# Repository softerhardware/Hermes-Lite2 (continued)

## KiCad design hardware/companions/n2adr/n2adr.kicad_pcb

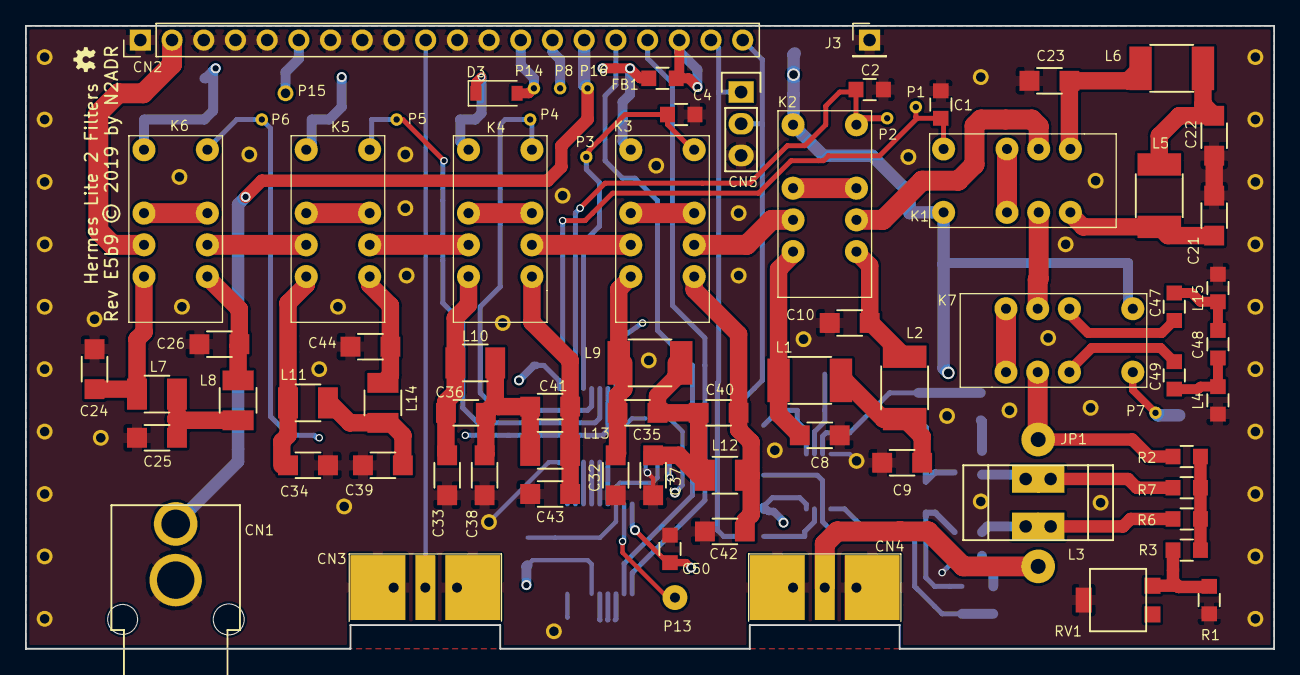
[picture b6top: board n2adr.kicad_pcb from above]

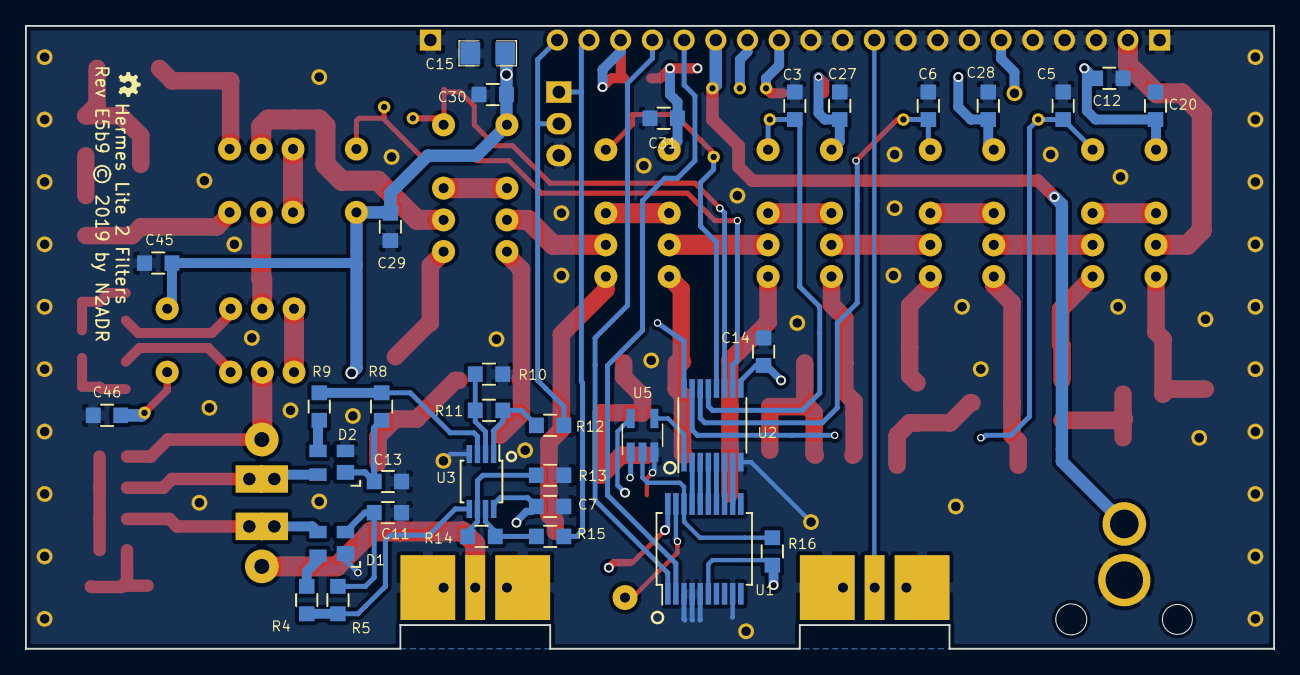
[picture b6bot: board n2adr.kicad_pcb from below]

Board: 4 copper layers, 100.0 x 49.9 mm, 112 parts (34 on the bottom side), 80 nets.

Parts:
C1, C2, C3, C4, C5, C6, C7, C11, C13, C14, C20, C27, C28, C29, C30, C31, C45, C46, C50: 100n; SMD_0805
C8, C10: 1000p; SMD_1206
C9, C21, C23: 1800p; SMD_1206
C12: 22uF; SMD_0805
C15: 100uF; SMD-1206
C22: 3300p; SMD_1206
C24, C26, C33: 150p; SMD_1206
C25, C39: 330p; SMD_1206
C32, C38, C40: 270p; SMD_1206
C34, C44: 180p; SMD_1206
C35: 100p; SMD_1206
C36: 39p; SMD_1206
C37: 560p; SMD_1206
C41, C42: 220p; SMD_1206
C43: 68p; SMD_1206
C47, C49: 1500p; SMD_0805
C48: 680p; SMD_0805
CN1: Audio-Jack-2; PhonoRcaRCJ-04x
CN2: Conn_01x20; Pin_Header_Straight_1x20_Pitch2.54mm
CN3, CN4: SMA; BNCEDGE
CN5: CONN_01X03; Pin_Header_Straight_1x03
D1, D2: BAS40-07; SOT-143
D3: 1N4148; D_SOD-123
FB1: FB; SMD_0805
J3: Conn_01x01; Pin_Header_Straight_1x01_Pitch2.54mm
JP1: 1T; WireConnection_1.20mmDrill
K1, K2, K3, K4, K5, K6, K7: EC2-3NU; RelayDPDT01
L1, L2: 1.8u; SMD_1812
L3: 10T; ToroidT37
L4, L15: 1.8u; SMD_0805
L5, L6: 3.9u; SMD_1812
L7, L8: 220n; SMD_1210
L9: 1000n; SMD_1812
L10: 560n; SMD_1210
L11, L14: 390n; SMD_1210
L12: 680n; SMD_1210
L13: 270n; SMD_1210
P1, P2, P3, P4, P5, P6, P7, P8, P14, P16: TST; WirePad_0.5mm
P13, P15: TST; SolderWirePad_single_0-8mmDrill
R1: 22 1%; SMD_0805
R2, R10, R13: 2K2 1%; SMD_0805
R3: 56 1%; SMD_0805
R4, R5, R8, R9: 4K7; SMD_0805
R6, R7: 18 1%; SMD_0805
R11, R14: 6K2 1%; SMD_0805
R12, R15: 330; SMD_0805
R16: DNI; SMD_0805
RV1: DNI; Trimpot_Bourns_3314G
U1: MCP23008; SSOP-20_5.3x7.2mm_Pitch0.65mm
U2: ULN2003LV; TSSOP-16_4.4x5mm_Pitch0.65mm
U3: AD8692; MSOP-8_3x3mm_Pitch0.65mm
U5: 74LVC1G00; SOT-23-5_HandSoldering

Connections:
+3V3: C7.2, C12.2, C14.2, C15.2, C20.2, C27.2, C28.2, C29.2, C30.2, C31.2, C45.2, C50.2, D3.1, FB1.1, K1.1, K2.1, K3.1, K4.1, K5.1, K6.1, K7.1, R16.1, U1.6, U1.20, U2.9, U3.8, U5.5
Band1: C1.2, K1.8, P1.1, U2.10
Band2: C2.2, K2.8, P2.1, U2.11
Band3: C4.2, K3.8, P3.1, U2.12
Band4: C3.2, K4.8, P4.1, U2.13
Band5: C6.2, K5.8, P5.1, U2.14
Band6: C5.2, K6.8, P6.1, U2.15
Band7: C46.2, K7.8, P7.1, U2.16
FilterOut: JP1.2, K7.6, R2.2
GND: C1.1, C2.1, C3.1, C4.1, C5.1, C6.1, C7.1, C8.1, C9.1, C10.1, C11.2, C12.1, C13.2, C14.1, C15.1, C20.1, C21.2, C22.2, C23.2, C24.1, C25.1, C26.1, C27.1, C28.1, C29.1, C30.1, C31.1, C32.1, C33.1, C34.1, C37.1, C38.1, C39.1, C42.1, C43.1, C44.1, C45.1, C46.1, C50.1, CN1.2, CN2.1, CN2.3, CN2.4, CN2.5, CN2.7, CN2.8, CN2.9, CN2.11, CN2.12, CN3.2, CN4.2, CN5.3, D1.1, D2.2, J3.1, L4.1, L15.1, R1.1, R10.1, R13.1, RV1.2, U1.3, U1.4, U1.5, U1.9, U2.8, U3.4, U5.3
INTTR: CN2.13, D3.2, P14.1, U5.1
unnamed: C8.2, K2.4, L1.1
unnamed: C9.2, L1.2, L2.1
unnamed: C10.2, K2.5, L2.2
unnamed: C11.1, D1.2, R5.2
unnamed: C13.1, D2.1, R8.2
unnamed: C21.1, K1.4, L5.1
unnamed: C22.1, L5.2, L6.1
unnamed: C23.1, K1.5, L6.2
unnamed: C24.2, K6.4, L7.1
unnamed: C25.2, L7.2, L8.1
unnamed: C26.2, K6.5, L8.2
unnamed: C32.2, C35.2, K3.4, L9.1
unnamed: C33.2, C36.2, K4.4, L10.1
unnamed: C34.2, K5.4, L11.1
unnamed: C35.1, C37.2, C40.2, L9.2, L12.1
unnamed: C36.1, C38.2, C41.2, L10.2, L13.1
unnamed: C39.2, L11.2, L14.1
unnamed: C40.1, C42.2, K3.5, L12.2
unnamed: C41.1, C43.2, K4.5, L13.2
unnamed: C44.2, K5.5, L14.2
unnamed: C47.1, C48.2, L15.2
unnamed: C47.2, K7.2
unnamed: C48.1, C49.2, L4.2
unnamed: C49.1, K7.7
unnamed: CN1.1, CN2.15, P16.1
unnamed: CN2.6, P15.1
unnamed: CN2.10, CN3.1
unnamed: CN2.14, P8.1
unnamed: CN2.16, U1.2
unnamed: CN2.17, U1.1
unnamed: CN2.18, FB1.2
unnamed: CN2.19, CN5.1, R15.2
unnamed: CN2.20, CN5.2, R12.2
unnamed: CN4.1, JP1.1
unnamed: D1.3, L3.1, R6.2
unnamed: D1.4, R4.2
unnamed: D2.3, R9.1
unnamed: D2.4, L3.2, R7.1
unnamed: K1.2, K1.7
unnamed: K1.3, K7.3
unnamed: K1.6, K2.6
unnamed: K2.2, K2.7
unnamed: K2.3, K3.6
unnamed: K3.2, K3.7
unnamed: K3.3, K4.6
unnamed: K4.2, K4.7
unnamed: K4.3, K5.6
unnamed: K5.2, K5.7
unnamed: K5.3, K6.6
unnamed: K6.2, K6.7
unnamed: K7.4, K7.5
unnamed: P13.1, U1.19
unnamed: R1.2, R3.1, RV1.1
unnamed: R2.1, R3.2, R6.1, R7.2
unnamed: R4.1, R5.1, U3.5
unnamed: R8.1, R9.2, U3.3
unnamed: R10.2, R11.1, U3.2
unnamed: R11.2, R12.1, U3.1
unnamed: R13.2, R14.1, U3.6
unnamed: R14.2, R15.1, U3.7
unnamed: R16.2, U1.18, U5.2
unnamed: U1.12, U2.7
unnamed: U1.13, U2.6
unnamed: U1.14, U2.5
unnamed: U1.15, U2.4
unnamed: U1.16, U2.3
unnamed: U1.17, U2.2
unnamed: U2.1, U5.4
RFInput: CN2.2, K6.3

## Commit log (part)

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2019-11-19 Rev 2 of rear end plate
2019-11-19 Swap horizontal and veritical lettering
2019-11-21 Rear end plate 40mm 2.0
2019-11-23 Updates to endplate
2019-11-24 55mm rev2 endplate
2019-11-25 Added pullups, diodes to some channels
2019-11-27 Added db9 adapter and smallio
2019-11-27 Updated hermeslite.lib
2019-11-30 Added io_jumper and psfeedback boards
2019-12-02 Final IO end plates
2019-12-02 Added BOM and generated gerber files
2019-12-02 Deleted old releases
2019-12-21 radioberry firmware and gateware added. 4rx (48k) and 1 tx (initial version)
2019-12-21 git ignore added
2019-12-21 build results removed
2019-12-22 making radioberry variants
2019-12-23 Assembly updates
2019-12-23 Assembly edits
2019-12-24 Added more assembly notes
2019-12-24 Fixed file name
2019-12-30 Added IO diagrams
2019-12-30 Added wiring diagram, increased PCB size
2019-12-30 Moved picture
2020-01-01 Added sym-lib-table and updated .sch to use only n2adr.lib
2020-01-08 improvement
2020-01-13 Added fan control, psync as generate, board id in discovery, fifo fixes
2020-01-18 Timing path fix in vna_scanner
2020-01-20 Stable release of 20191110_68p4, testing release of 20190119_69p0
2020-01-25 radioberry: use of iq fifo improved
2020-01-25 radioberry: tx and some improvements
2020-02-03 Fix for receivers number of 2,3,5 and 6
2020-02-03 Fix link
2020-02-03 radioberry build for new radio.v
2020-02-09 tx improvement
2020-02-11 First CWX support
2020-02-13 Release 69p2
2020-02-13 Added cw_openhpsdr
2020-02-14 Added cw_basic and led_flash
2020-02-22 Work on restructured FSM for TX
2020-02-23 20200222_69p3 release
2020-02-23 Updated 69p3 release notes
2020-03-01 cwx supported by radioberry
2020-03-02 Multi RX 3 working again, updates for autotuner, 69.4 testing
2020-03-02 ATU details
2020-03-02 Testing release 69.4
2020-03-06 radioberry 69p4
2020-03-09 Updated end plate README
2020-03-22 Add LPF for fan on latest end plates
2020-03-22 Support for factory and field gateware images in EEPROM
2020-03-23 Minor updates to schematic text
2020-03-23 Parameterized fast LNA, only set during RX
2020-03-28 Working LNA adjust during TX
2020-03-30 Release 20200329
2020-03-30 Release 20200329 bitfiles
2020-03-30 Change in size to SMA cutout
2020-03-31 Added missing remote_update.v
2020-04-21 Relax factory test
2020-04-21 Allow scaling of coefL4
2020-04-21 fan changes
2020-04-21 cwx fix to not accumulate data in TX buffer
2020-04-25 20200425_71p1 release
2020-04-26 Update hl2setup program for next production run
2020-04-28 gateware 71.1; LNA gain fast + CWX update
2020-05-03 Alex rx antenna
2020-05-04 revert fast LNA and increased tx pwr
2020-05-05 updated timing
2020-05-06 Switched to IAMP TX gain based on Hermes-Lite 1
2020-05-07 Radioberry TX; (version 71.3)
2020-05-16 Tighten timing on PGA5
2020-05-16 Simulation cleanup, add parameter to debug RX
2020-05-17 20200516_71p2 release
2020-05-23 Relaxed no filter 160M test
2020-05-29 Output register for UART
2020-05-29 Fix for no CW in SDR Console
2020-05-29 Fix for github issue 145
2020-05-30 71p3 and support to reset Versa5
2020-05-30 Release 71p3
2020-06-05 Added link to HR50 notes
2020-06-08 71p4 + ptt/key info to firmware/SDR program
2020-06-29 Moved 71p3 to stable, built all variants, clean-up of variants
2020-06-29 Ready for 72 series with hl2link
2020-06-30 2020069 72p0 relesae
2020-06-30 added and modified files for AK4951 Companion Board Version 3
2020-07-01 Updates to ak4951 variant to use generate, rerelease of hl2b5up_6rx
2020-07-01 Added hl2b3to4_cicrx and hl2b5up_15ce
2020-07-05 Added ak4951v3
2020-07-07 keyer CW
2020-07-11 i2c with clock sync working
2020-07-13 Experimental Release
    Please enter the commit message for your changes. Lines starting
2020-07-24 First working discovery on second ethernet port, updates to hl2link
2020-07-25 Reformat and align RTL
2020-07-25 Switch CDC in udp_destination to one way handshake
2020-07-27 Added extra discover fields, fixed ARP CDC, extra byte in UDP
2020-07-28 20200727_72p2 testing release
2020-08-04 Working response with port 1025
2020-08-04 Added hermeslite.py
2020-08-04 Release 20200803_72p3
2020-08-23 Updated hermeslite.py, added stable/latest link
2020-08-23 Fixed github gateware update
2020-08-23 Updated hermeslite.py README.md
2020-08-23 Fixed typos
2020-08-23 Proper typo fixes
2020-08-24 Updated hermeslite.py, added Jupyter notebook
2020-09-14 Synchronized command passing over link working
2020-09-19 New command mapping for sync and clock use
2020-09-20 Work on receive RX data in master
2020-09-28 Slave receive properly passed to master
2020-10-19 72p4 release
2020-10-19 move to archive
2020-10-19 Added 72p4 bitfiles
2020-11-01 Added receiver_4000
2020-11-03 Updated Band Volts to co-exist with Fan PWM. Selection via Dither bit.
2020-11-03 Adjusted for 3.3V power supply
2020-11-03 Added band voltage PWM output.
2020-11-08 Added keyup to CWX, increased watchdog timeout
2020-11-08 Restructured to avoid timing path
2020-11-08 Added write_ad9866
2020-11-08 20201107_72p5 testing release
2020-11-12 gateware 72.1
2020-11-12 gateware 72
2020-11-14 radioberry; gateware 72.2; local CW pihpsdr; using RB connector(CN301) to connect paddle
2020-11-16 72.3 radioberry; sync channel changes
2020-11-16 4k radioberry
2020-11-22 Add option to enable debug instrumentation
2020-11-22 Support for new debug instrumentation
2020-11-22 20201121_72p6 release
2020-11-22 Corrected syntax
2020-11-26 Added heatshim
2020-11-28 Initial attempt to improve the DHCP handling.
2020-11-28 Make sure that we revert to doing a DHCP discover after the network cable is unplugged and reconnected. Also, ask, in the DHCP DISCOVER for the IP address that we want.
    Also, don't respond to pings that are unicast to us when the IP address
    doesn't match. This fixes a problem where the DHCP server thinsks that
    our requested address is already in use by another system!
2020-11-28 192kHz cic only 10 receivers
2020-11-28 Release 72p7
2020-12-01 Use the configured IP to set the client address. Also include the ip_id so that we can count IP packets being sent to see where they are lost.
2020-12-01 Rename a poorly named signal
2020-12-03 Removed ip_id to fix timing
2020-12-06 radioberry 72.4
2020-12-09 Removed numpy from debug, small changes to hermeslite.py
2020-12-09 Updates to hl2link for sync receivers
2020-12-09 hl2b3to4 10rx working
2020-12-09 Added VERSA_BYPASS parameter for new variant
2020-12-13 TX buffer latency to 20ms, PTT Hangtime to 12ms
2020-12-13 HL2 Link refinements for synced receivers
2020-12-13 Prepare for 72.8 release
2020-12-13 20201212_72p8 release
2020-12-17 FAN/ATU clarifications
    Clearing up some items that tripped me up.
2020-12-19 Moved 20201212_72p8 to stable, fixes in hermeslite.py
2020-12-19 radioberry 72.5 version
2020-12-24 radioberry 4k
2020-12-31 Adjust value to get the port number correctly.
2020-12-31 Fix the use of tabs
2020-12-31 Improve the comment
2021-01-02 Add ft8 work
2021-01-03 added my endcaps with higher airflow
2021-01-05 ft8 work
2021-01-09 Added Python fortran wrapper
2021-02-16 radioberry gateware 73.0; support of PA board
2021-03-30 Added bypassversa
2021-04-29 Changed initialisation of tx_gain to reflect initialised value in ad9866.
2021-05-10 link updates, includes crc
2021-05-10 Added support to stay in TX mode until software says to go to RX
2021-05-10 73p0 testing release
2021-05-16 New testing with debug enabled
2021-05-16 Testing release 20210516_73p1
2021-06-24 gateware-radioberry-juice
2021-07-08 hermeslite.py: discover HL2s on all interfaces
2021-07-10 Added 10MHz config to Clk1 and Clk2
    In 1 new function, Clk1 is configured for external 10Mhz clock source and then Clk2 is configure to output 10Mhz, useful for chaining the 10Mhz on to a transverter or test equipment. This appears to 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
2021-07-10 Configure both Clk1 and Clk2 to 10Mhz in one function
2021-07-22 Merged 10MHz setup from K7MDL
2021-07-31 73p2 Testing Release
2021-08-05 20210730_73p2 release with all variants
2021-08-09 Moved 20210730_73p2 to stable
2021-08-19 Update README.md
    Removed 'testing' from README now that is is moved to 'stable'.
2021-08-28 juice tx without preamp
2021-09-11 radioberry 73.2 8bits rx + tx spi
2021-09-12 replaced sidetone module to reduce FPGA resources and revive 4rx and PS.
2021-09-22 fixed excessive AK4951 microphone gain
2021-09-26 rx iq 8 bit improvement
2021-09-27 added Key-Down delay function
2021-09-28 build for 4K as well
2021-09-29 fixed abnormal CW code duty if breakin is OFF setting
2021-09-29 git ignores and build improved for radioberry
2021-10-05 Added iambic Mode-B dot memory inhibit period.
2021-12-12 Added reboot
2021-12-12 Proper i2c output drivers
2021-12-12 Timing closure work for 6RX variant
2021-12-12 Placement directive for timing closure with many receivers
2021-12-12 First NCO support for efinix
2021-12-12 Switch to release 74p0
2021-12-13 Restructured NCO for efinix porting
2021-12-13 Added 2.4MHz gateware
2022-01-10 support keyer and local CW hang management
2022-01-10 Bug fixes for last commit
2022-01-10 Added 202220109_73p3 testing release
2022-01-12 hermeslite.py: enhance ability to embed
    1) make discover path verbosity tunable if desired
    >= 2: all output; 1: output only on discovery; 0: no output
    2) make command function timeout and attempts tunable if desired
2022-01-14 rb-juice beta2
2022-01-21 cl016 juice
2022-01-24 rb 73.3
2022-02-02 Adding cicrx for Radioberry juice variants.
2022-02-03 Fixes for including files.tcl without conflicting with receiver_nco.v since the cicrx variants use receiver_ciconly.v
2022-02-04 This should have been included in the previous: Fixes for including files.tcl without conflicting with receiver_nco.v ...
2023-01-14 Updates for new LDMOS devices
2023-05-03 Additions to hermeslite.py from N2ADR
2023-07-27 Typo fix from N2ADR
2023-11-25 Updated to add inhibit signal into protocol for return to PC
2023-11-27 Release cleanup
2023-11-28 Added release to Makefile
2023-12-07 Testing release for TxInhibit propagation
2023-12-08 Corrected the inversion of the (active low) Txinhibit signal as sent in the protocol
2023-12-08 Made 20231208_74p1_a0bcd34 release, with release automation
2023-12-29 Fix for incorrect response to cwx bits if cwx disabled but cw is used during SSB or other mode
2023-12-31 Update version minor
2023-12-31 Added testing release 20231230_74p2_883a338
2024-01-08 Added testing 74p2 rbf files of ak4951 variants
    ak4951v4 is for v4 board that supports ATU, ak4951v3 is for v3 that doesn't support ATU.
2024-01-08 Updated README.md of testing 74p2 release
    Updated the discription about ak4951 variant
2024-03-03 Moved latest testing to stable
2024-03-03 Added audio_included and relax_sequencing
2024-03-03 Added experimental
2024-04-16 Update Python Module README with netifaces info, example
    Add info on finding the netifaces python module. While it's still widely available via forks and downstream projects the module is no longer officially supported. Also provided a pointer to the addre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
2024-12-09 Added website
2024-12-09 Path update test
2024-12-09 Added nojekyll
2024-12-09 Removed not working forkme ribbon
2024-12-09 Create CNAME
2025-01-03 Controll the VNA-Feature at the top-file.
2025-07-24 radioberry cl025 pio mode for rpi-5 and rp1 (pcie)
2025-08-14 radioberry pi5-pio mode tx improvement
2025-09-10 radioberry rpi-5 pio mode
